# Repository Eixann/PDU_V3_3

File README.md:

**PDU_V3_3** is the power distribution board of the ORCA UGM underwater vehicle. It switches the 4S thruster battery
to 8 thruster ESCs through 8 Infineon PROFET+2 high-side switches (BTS70012-1ESP, one per thruster), measures the
current of every channel, and cuts all thrusters when the kill switch is pulled.

The PROFET channel and current-sense chain are copied from
[dingoPDM-Max](https://github.com/corygrant/dingoPDM-Max) (V1.2 schematic p.7-11).

- **Input:** QS8-S anti-spark connector (J1), soldered to a 5 mm copper VBAT busbar (BB1)
- **Outputs:** 4 right-angle XT60PW (J5-J8) + 2 stacked XT60 (J14, J15) for the upper board (V2_atas), 2 stacked XT60 GND (J12, J13)
- **Protection per channel:** short-circuit latch-off (~3 µs), over-temperature, BYG23M flyback, 10 nF output cap; SMCJ17A TVS on VBAT
- **Current sense:** IS → 1.2 kΩ → 3V3 zener clamp → LM324 follower → ADS7828 (12-bit, I2C 0x48) on J3
- **Kill:** XT30 (J2) switched battery → TSR 1-2450 → `KILL_EN` → IN/DEN of all 8 PROFETs

> [!WARNING]
> This board was designed by students for a research vehicle, not by a professional. Use it at your own risk; the
> designers are not responsible for damage or injury. The busbars (BB1, BB2, BB3) are **mandatory**: without them the
> copper reaches >100 °C at 14 A per thruster.

---

## Specifications

| Item | Value |
| --- | --- |
| Battery | 4S Li-ion/LiPo, 16.8 V max (PROFET V<sub>S(NOR)</sub> 6-18 V, abs. max 28 V) |
| Channels | 8 × BTS70012-1ESP, 1 thruster each |
| Design current | 14 A per thruster continuous (112 A total), simulated T<sub>j</sub> 58-61 °C with busbars |
| Board | 118.2 × 113.6 mm, 2 layers, 2 oz copper, 1.6 mm |
| Logic | +5 V (TSR 1-2450) → +3V3 (LD1117S33), always on |
| ADC | ADS7828 @ 0x48, internal reference on (PD1 = 1), I ≈ code / 58.3 A |
| Fault | latched fault reads ≥ 2000 codes (≈ 2950 typ.); reset = IN low ≥ 100 ms (pull the kill) |

---

## Channel Map

The OUT2/OUT3 connectors were swapped so every output lane stays on one copper layer. Firmware must use this table.

| Connector pin | Net / PROFET | ADS7828 channel |
| --- | --- | --- |
| J14.2 (stack) | OUT1 / U101 | CH7 |
| J5.2 | OUT2 / U201 | CH4 |
| J14.1 (stack) | OUT3 / U301 | CH5 |
| J6.2 | OUT4 / U401 | CH6 |
| J7.2 | OUT5 / U501 | CH1 |
| J8.2 | OUT6 / U601 | CH2 |
| J15.2 (stack) | OUT7 / U701 | CH0 |
| J15.1 (stack) | OUT8 / U801 | CH3 |

J3 (JST-XH 4p to the Jetson): pin 1 NC, pin 2 SDA, pin 3 SCL, pin 4 GND.

> [!IMPORTANT]
> The Jetson/Pixhawk run from a separate battery, but their ground is already joined to the thruster ground through
> the ESC PWM leads and J3. Bond the system ground to a BB2 GND bolt with one 18-20 AWG wire so this current does
> not flow in the thin signal wires, twist SDA/SCL and every PWM lead with its ground, and do not connect the ESC
> BEC (red) wires to the Pixhawk.

---

## Notes

- Open the project with **KiCad 9**. Saving it in KiCad 10 makes it unreadable for KiCad 9.
- The QS8-S footprint comes from a measured part; there is no official QS8-S drawing.
- Upper board: `V2_atas/` (PCB only, no schematic). It stacks on J14/J15 and carries 4 XT60PW outputs; its channel labels follow the OUT2/OUT3 swap in the Channel Map.
- Busbar cut drawing (BB1/BB2/BB3): `PDU_V3_3/PDU_V3_3_busbars.dxf`. Gerbers, BOM and pick-and-place are exported from KiCad.
- Bottom side:

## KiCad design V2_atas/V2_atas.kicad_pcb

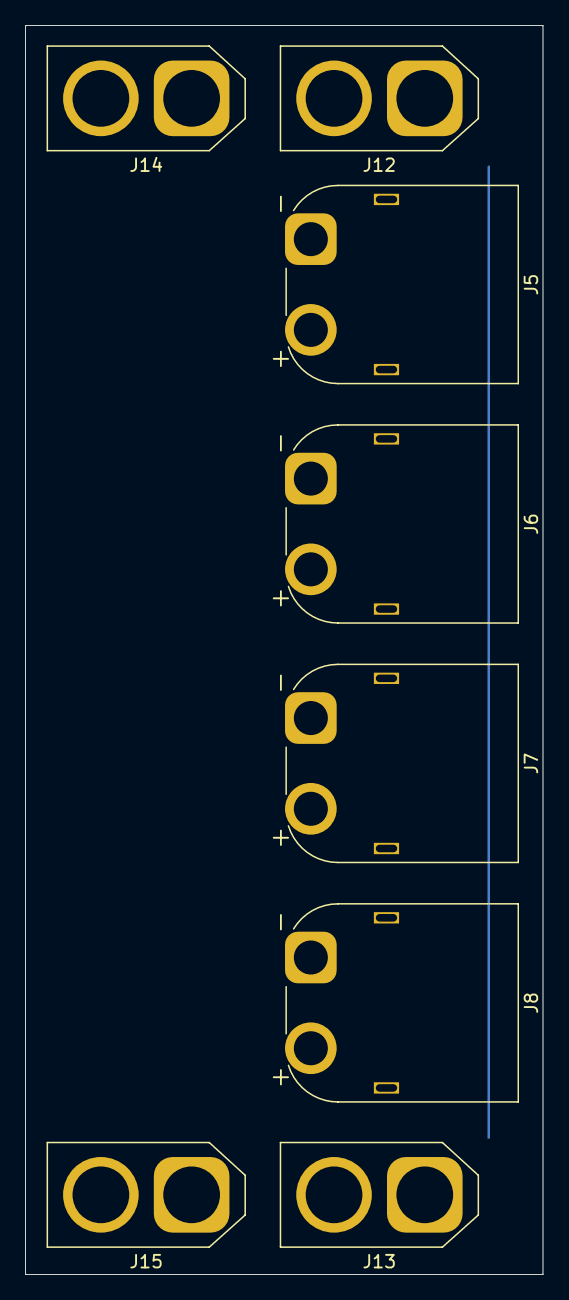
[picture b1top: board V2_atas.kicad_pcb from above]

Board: 2 copper layers, 41.1 x 99.1 mm, 8 parts (0 on the bottom side), 5 nets, no tracks yet.

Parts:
J5, J6, J7, J8: XT60-M; AMASS_XT60PW-M_1x02_P7.20mm_Horizontal
J12, J13, J14, J15: XT60-M; AMASS_XT60-M_1x02_P7.20mm_Vertical

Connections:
GND: J5.1 (NEG), J6.1 (NEG), J7.1 (NEG), J8.1 (NEG), J12.1 (NEG), J12.2 (POS), J13.1 (NEG), J13.2 (POS)
OUT1: J6.2 (POS), J14.2 (POS)
OUT3: J5.2 (POS), J14.1 (NEG)
OUT7: J7.2 (POS), J15.2 (POS)
OUT8: J8.2 (POS), J15.1 (NEG)

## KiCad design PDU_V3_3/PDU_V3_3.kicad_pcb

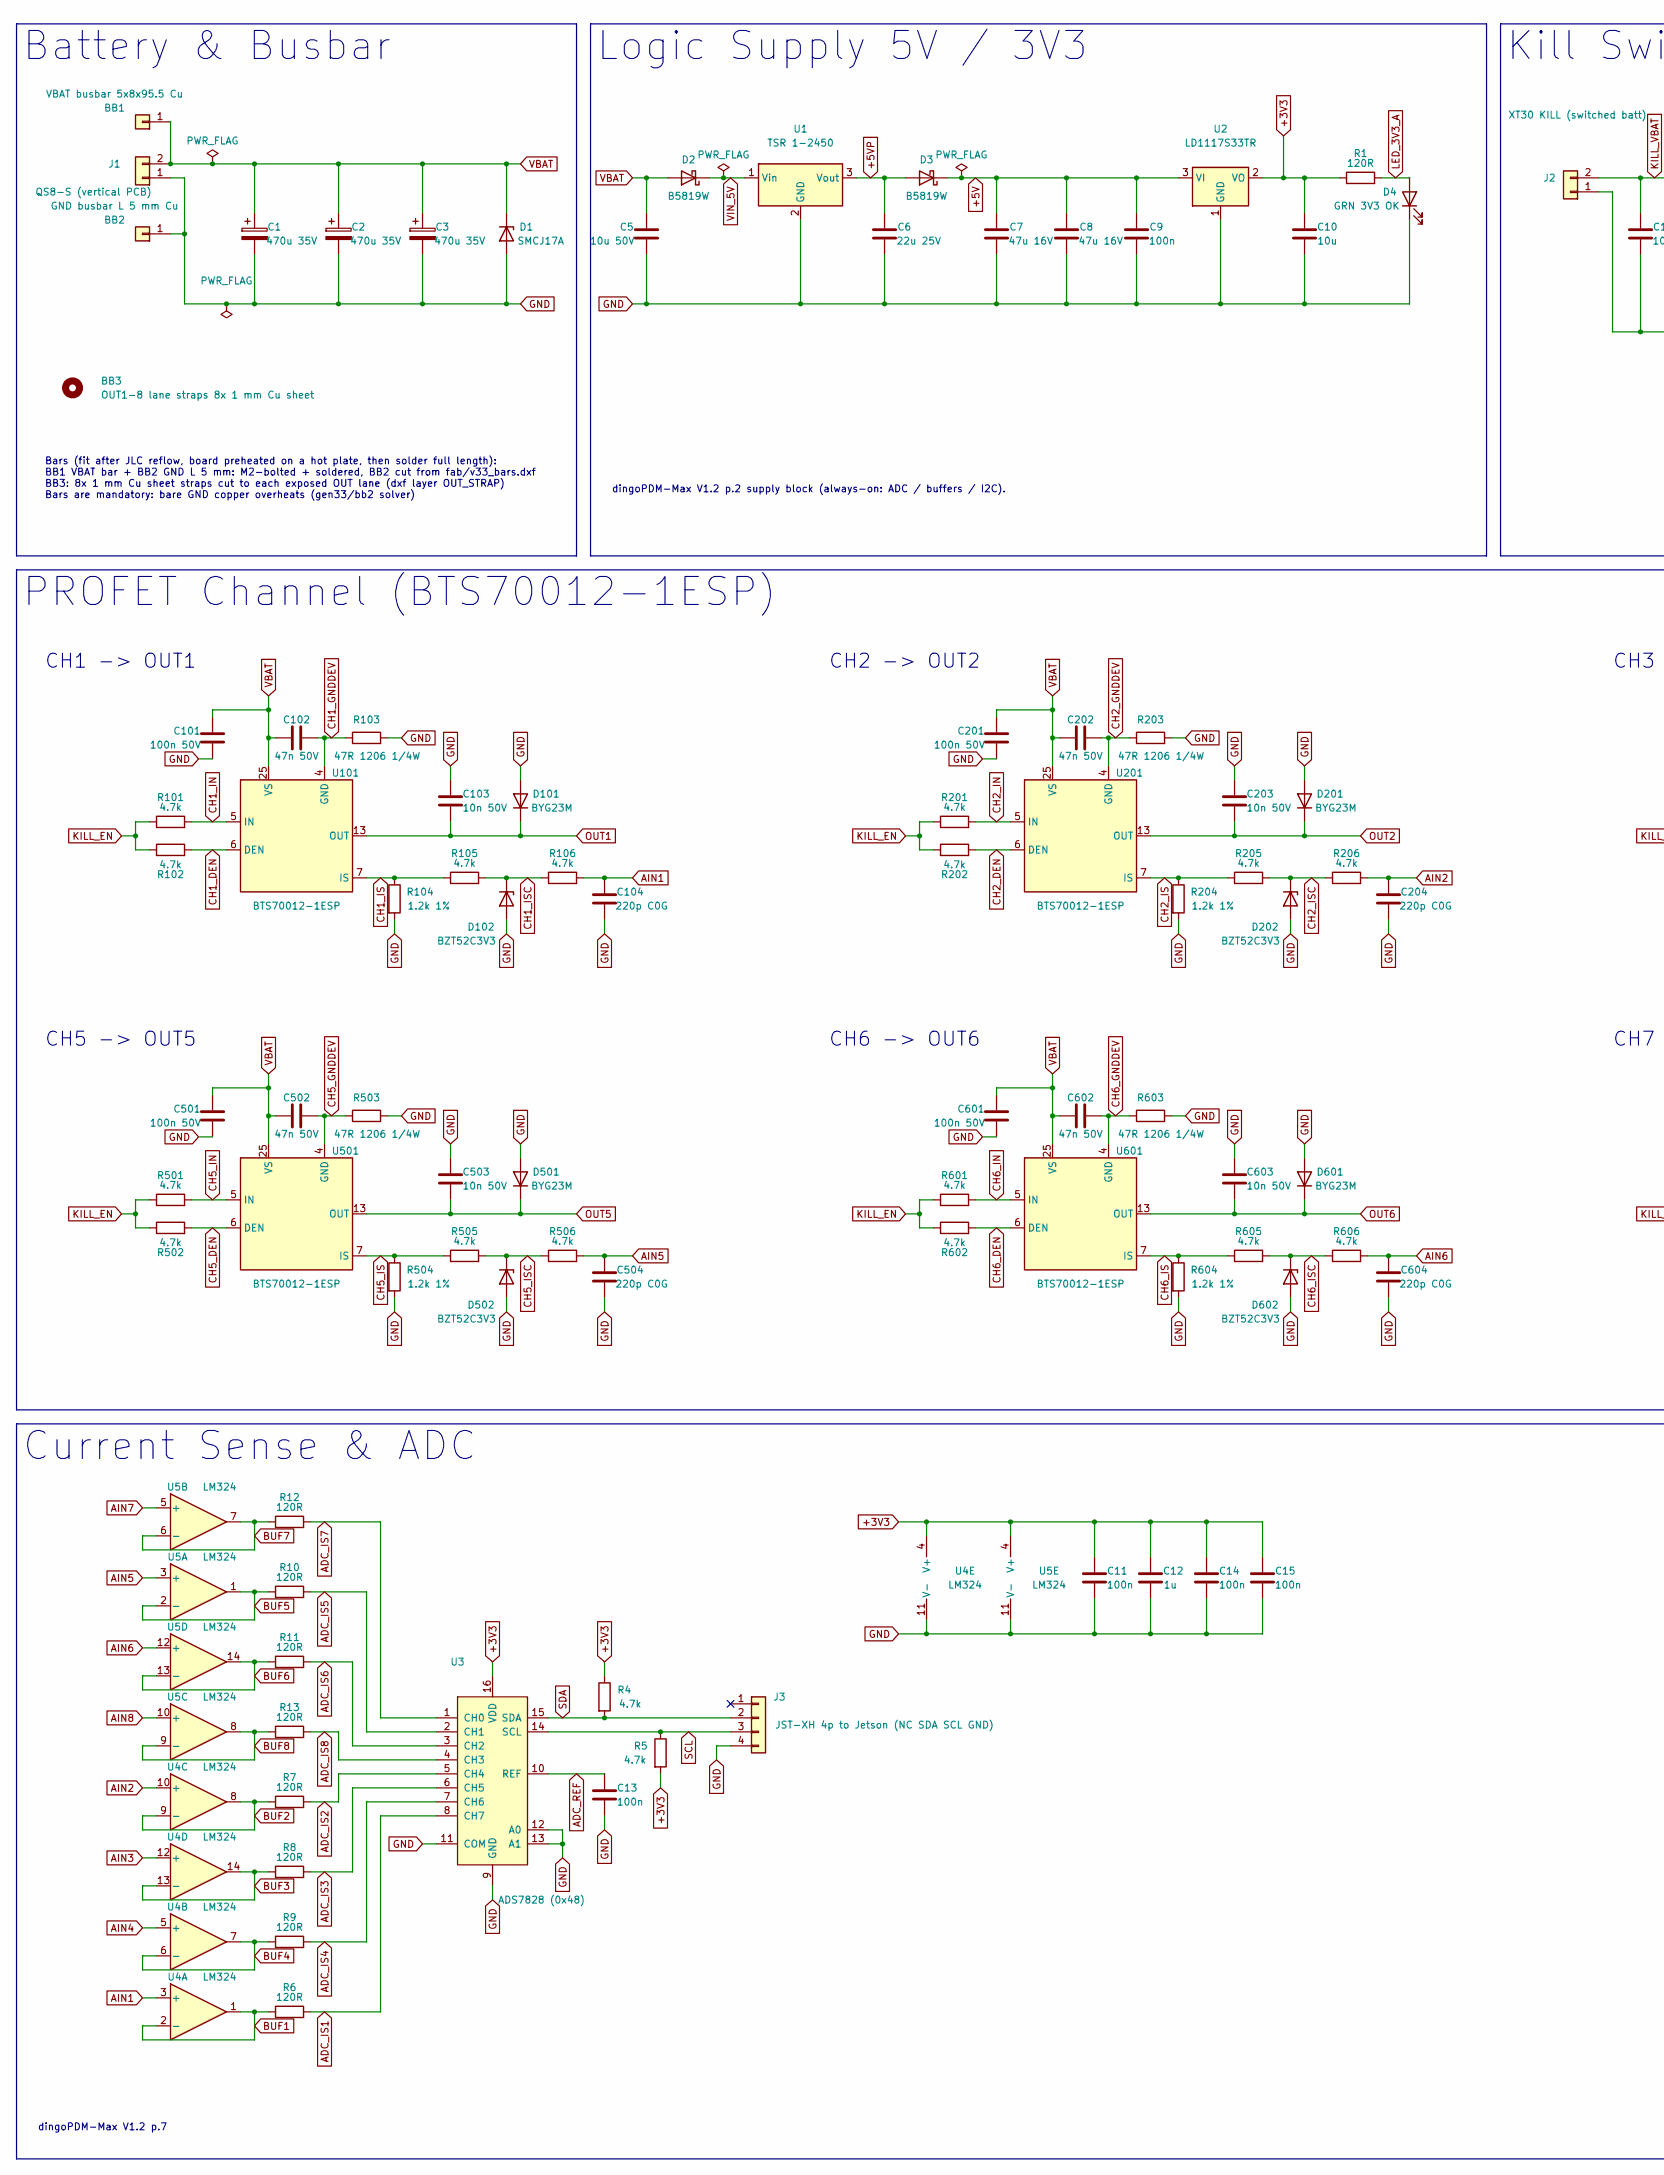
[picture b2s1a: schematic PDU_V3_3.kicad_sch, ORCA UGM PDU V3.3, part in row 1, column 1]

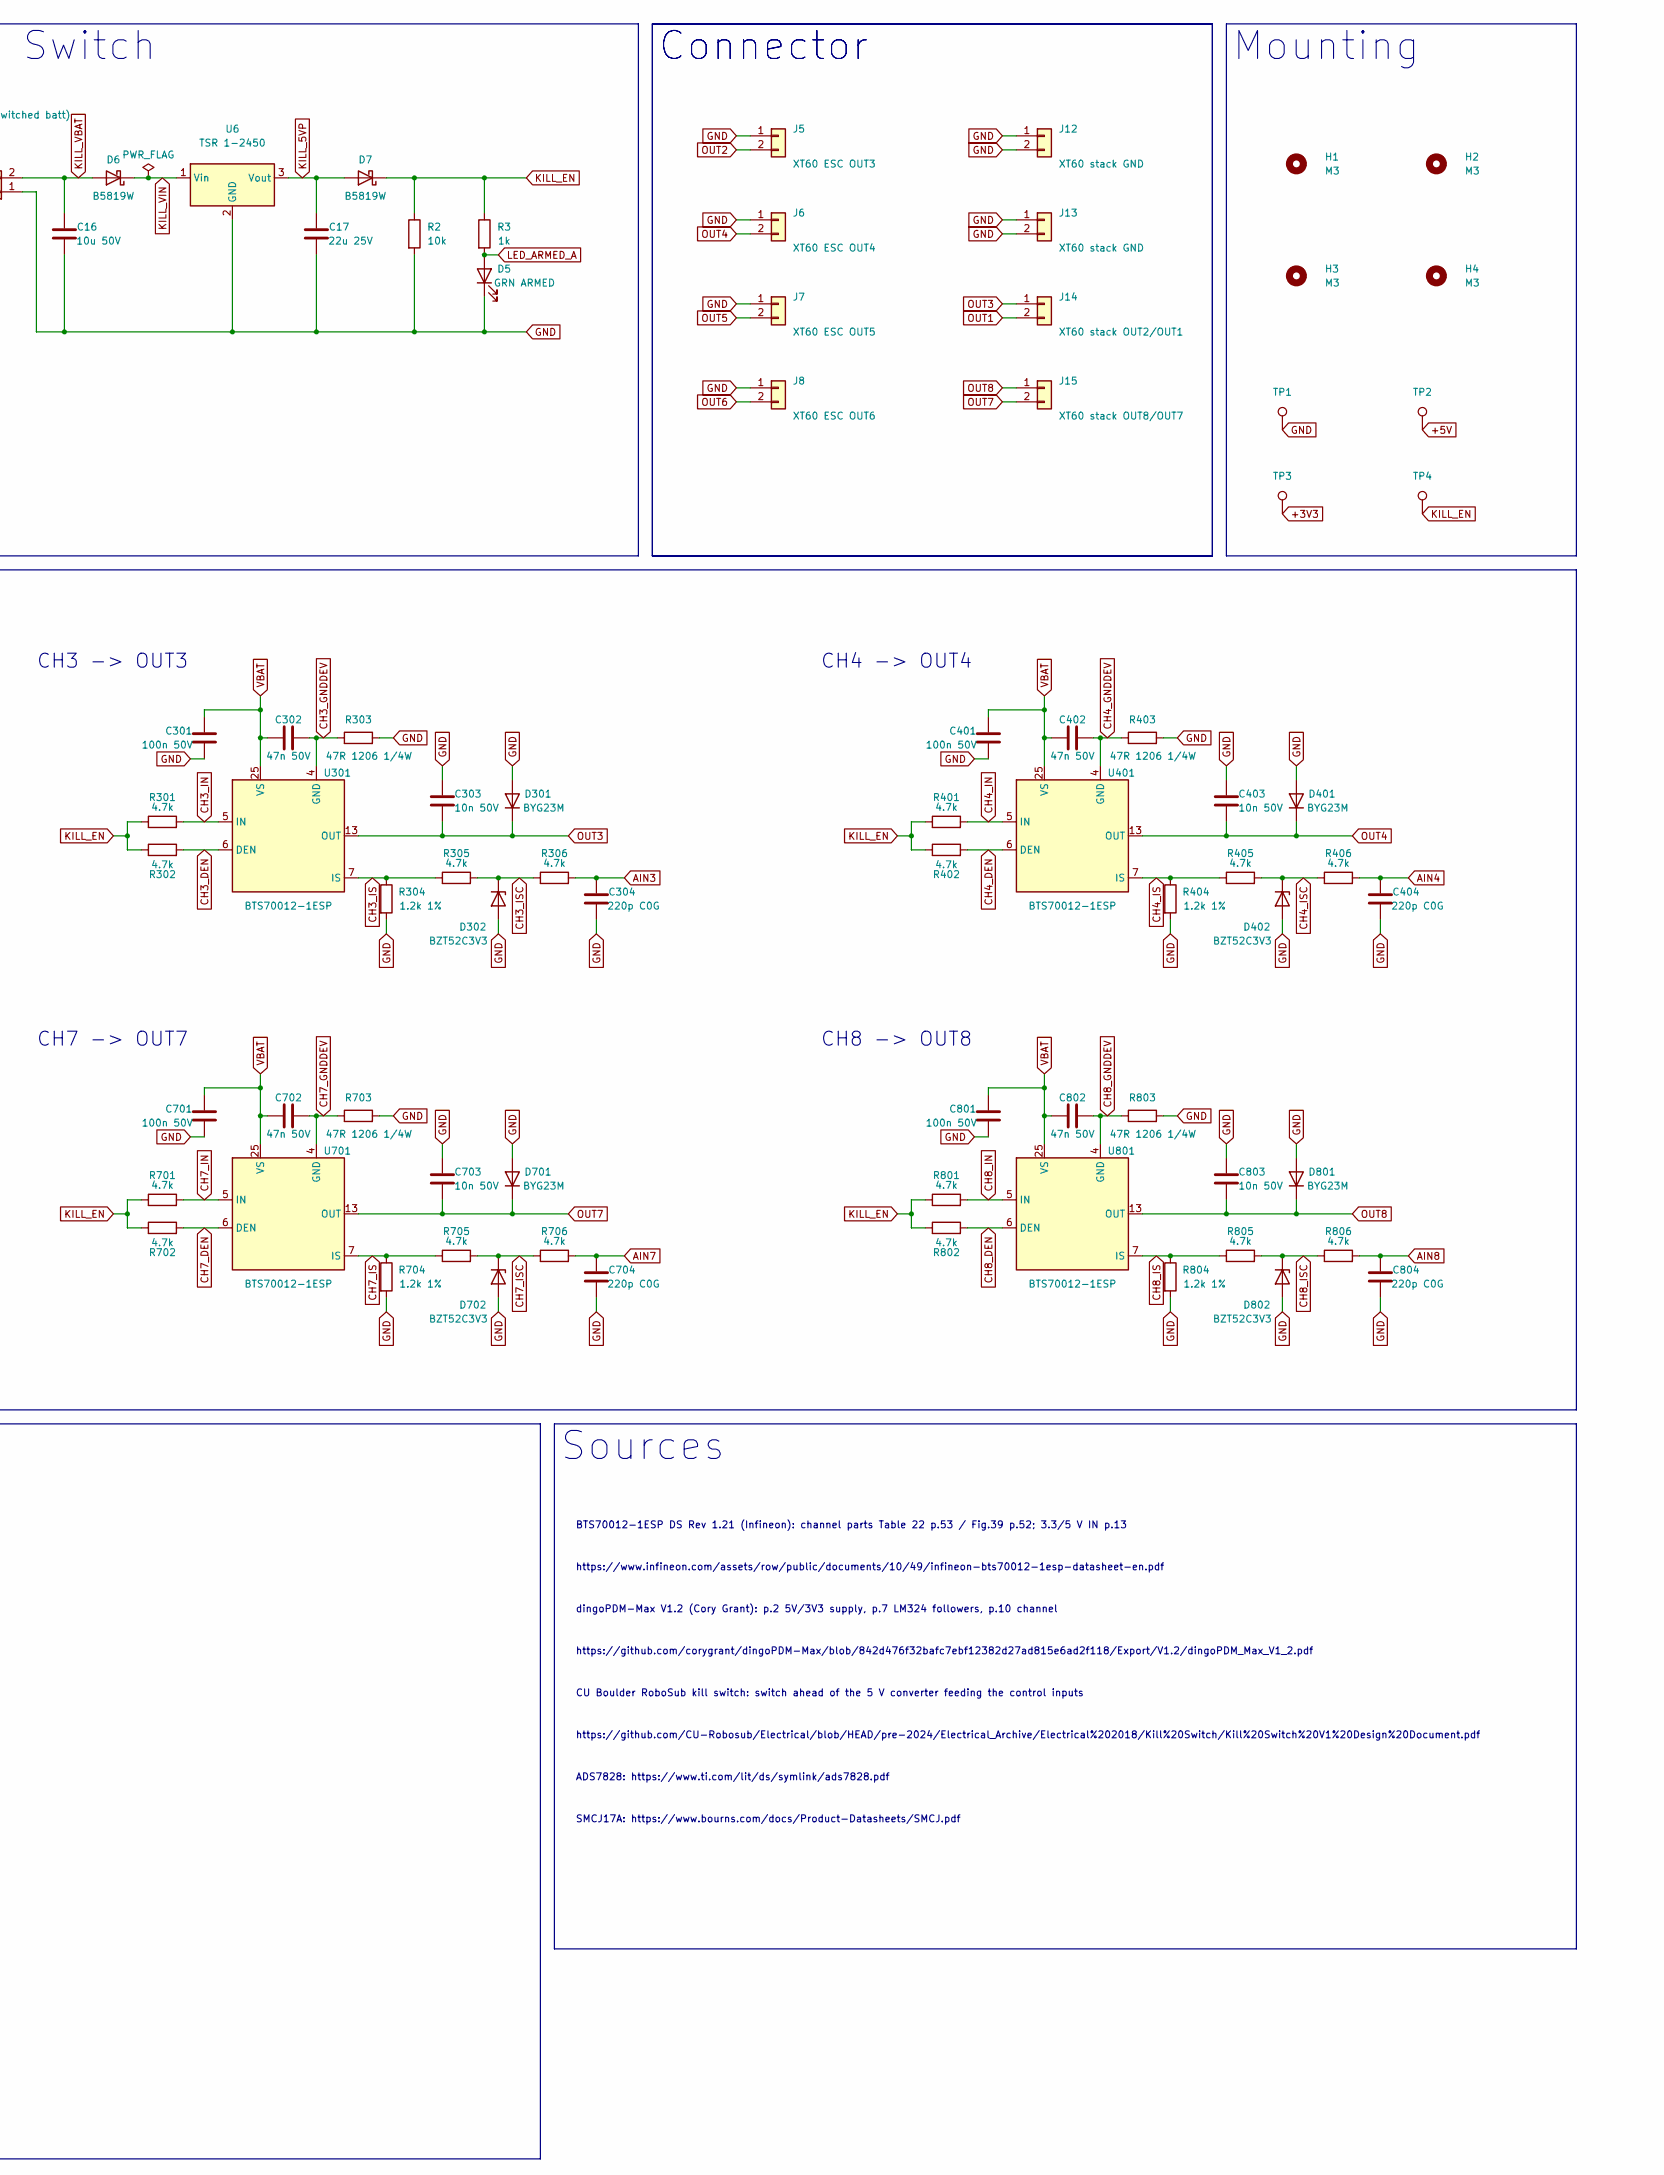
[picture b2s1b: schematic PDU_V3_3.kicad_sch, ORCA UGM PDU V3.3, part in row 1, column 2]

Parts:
BB1: VBAT busbar 5x8x95.5 Cu; Busbar_VBAT_5x8x92
BB2: GND busbar L 5 mm Cu; Busbar_GND_L_5x8
BB3: OUT1-8 lane straps 8x 1 mm Cu sheet
C1, C2, C3: 470u 35V; CP_Radial_D10.0mm_P5.00mm
C5, C16: 10u 50V; C_1206_3216Metric
C6, C17: 22u 25V; C_1206_3216Metric
C7, C8: 47u 16V; C_1206_3216Metric
C9, C11, C13, C14, C15: 100n; C_0603_1608Metric
C10: 10u; C_0805_2012Metric
C12: 1u; C_0603_1608Metric
C101, C201, C301, C401, C501, C601, C701, C801: 100n 50V; C_0603_1608Metric
C102, C202, C302, C402, C502, C602, C702, C802: 47n 50V; C_0603_1608Metric
C103, C203, C303, C403, C503, C603, C703, C803: 10n 50V; C_0603_1608Metric
C104, C204, C304, C404, C504, C604, C704, C804: 220p C0G; C_0603_1608Metric
D1: SMCJ17A; D_SMC
D2, D3, D6, D7: B5819W; D_SOD-123
D4: GRN 3V3 OK; LED_0603_1608Metric
D5: GRN ARMED; LED_0603_1608Metric
D101, D201, D301, D401, D501, D601, D701, D801: BYG23M; D_SMA
D102, D202, D302, D402, D502, D602, D702, D802: BZT52C3V3; D_SOD-123
H1, H2, H3, H4: M3; MountingHole_3.2mm_M3
J1: QS8-S (vertical PCB); AMASS_QS8S
J2: XT30 KILL (switched batt); AMASS_XT30PW-M_1x02_P2.50mm_Horizontal
J3: JST-XH 4p to Jetson (NC SDA SCL GND); JST_XH_B4B-XH-A_1x04_P2.50mm_Vertical
J5: XT60 ESC OUT3; AMASS_XT60PW-M_GNDpegs
J6: XT60 ESC OUT4; AMASS_XT60PW-M_GNDpegs
J7: XT60 ESC OUT5; AMASS_XT60PW-M_GNDpegs
J8: XT60 ESC OUT6; AMASS_XT60PW-M_GNDpegs
J12, J13: XT60 stack GND; AMASS_XT60-M_1x02_P7.20mm_Vertical
J14: XT60 stack OUT2/OUT1; AMASS_XT60-M_1x02_P7.20mm_Vertical
J15: XT60 stack OUT8/OUT7; AMASS_XT60-M_1x02_P7.20mm_Vertical
R1, R6, R7, R8, R9, R10, R11, R12, R13: 120R; R_0603_1608Metric
R2: 10k; R_0603_1608Metric
R3: 1k; R_0603_1608Metric
R4, R5, R101, R102, R105, R106, R201, R202, R205, R206, R301, R302, R305, R306, R401, R402, R405, R406, R501, R502, R505, R506, R601, R602, R605, R606, R701, R702, R705, R706, R801, R802, R805, R806: 4.7k; R_0603_1608Metric
R103, R203, R303, R403, R503, R603, R703, R803: 47R 1206 1/4W; R_1206_3216Metric
R104, R204, R304, R404, R504, R604, R704, R804: 1.2k 1%; R_0603_1608Metric
TP1: GND; TestPoint_Pad_D1.5mm
TP2: +5V; TestPoint_Pad_D1.5mm
TP3: +3V3; TestPoint_Pad_D1.5mm
TP4: KILL_EN; TestPoint_Pad_D1.5mm
U1, U6: TSR 1-2450; Converter_DCDC_TRACO_TSR-1_THT
U2: LD1117S33TR; SOT-223-3_TabPin2
U3: ADS7828 (0x48); TSSOP-16_4.4x5mm_P0.65mm
U4, U5: LM324; SOIC-14_3.9x8.7mm_P1.27mm
U101, U201, U301, U401, U501, U601, U701, U801: BTS70012-1ESP; Infineon_PG-TSDSO-24_ThermalVias

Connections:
+3V3: C10.1, C11.1, C12.1, C14.1, C15.1, R1.1, R4.1, R5.2, TP3.1, U2.2 (VO), U3.16 (VDD), U4.4 (V+), U5.4 (V+)
+5V: C7.1, C8.1, C9.1, D3.1 (K), TP2.1, U2.3 (VI)
+5VP: C6.1, D3.2 (A), U1.3 (Vout)
ADC_IS1: R6.2, U3.8 (CH7)
ADC_IS2: R7.2, U3.5 (CH4)
ADC_IS3: R8.2, U3.6 (CH5)
ADC_IS4: R9.2, U3.7 (CH6)
ADC_IS5: R10.2, U3.2 (CH1)
ADC_IS6: R11.2, U3.3 (CH2)
ADC_IS7: R12.2, U3.1 (CH0)
ADC_IS8: R13.2, U3.4 (CH3)
ADC_REF: C13.1, U3.10 (REF)
AIN1: C104.1, R106.2, U4.3 (+)
AIN2: C204.1, R206.2, U4.10 (+)
AIN3: C304.1, R306.2, U4.12 (+)
AIN4: C404.1, R406.2, U4.5 (+)
AIN5: C504.1, R506.2, U5.3 (+)
AIN6: C604.1, R606.2, U5.12 (+)
AIN7: C704.1, R706.2, U5.5 (+)
AIN8: C804.1, R806.2, U5.10 (+)
BUF1: R6.1, U4.1, U4.2 (-)
BUF2: R7.1, U4.8, U4.9 (-)
BUF3: R8.1, U4.13 (-), U4.14
BUF4: R9.1, U4.6 (-), U4.7
BUF5: R10.1, U5.1, U5.2 (-)
BUF6: R11.1, U5.13 (-), U5.14
BUF7: R12.1, U5.6 (-), U5.7
BUF8: R13.1, U5.8, U5.9 (-)
CH1_DEN: R102.2, U101.6 (DEN)
CH1_GNDDEV: C102.2, R103.1, U101.4 (GND)
CH1_IN: R101.2, U101.5 (IN)
CH1_IS: R104.1, R105.1, U101.7 (IS)
CH1_ISC: D102.1 (K), R105.2, R106.1
CH2_DEN: R202.2, U201.6 (DEN)
CH2_GNDDEV: C202.2, R203.1, U201.4 (GND)
CH2_IN: R201.2, U201.5 (IN)
CH2_IS: R204.1, R205.1, U201.7 (IS)
CH2_ISC: D202.1 (K), R205.2, R206.1
CH3_DEN: R302.2, U301.6 (DEN)
CH3_GNDDEV: C302.2, R303.1, U301.4 (GND)
CH3_IN: R301.2, U301.5 (IN)
CH3_IS: R304.1, R305.1, U301.7 (IS)
CH3_ISC: D302.1 (K), R305.2, R306.1
CH4_DEN: R402.2, U401.6 (DEN)
CH4_GNDDEV: C402.2, R403.1, U401.4 (GND)
CH4_IN: R401.2, U401.5 (IN)
CH4_IS: R404.1, R405.1, U401.7 (IS)
CH4_ISC: D402.1 (K), R405.2, R406.1
CH5_DEN: R502.2, U501.6 (DEN)
CH5_GNDDEV: C502.2, R503.1, U501.4 (GND)
CH5_IN: R501.2, U501.5 (IN)
CH5_IS: R504.1, R505.1, U501.7 (IS)
CH5_ISC: D502.1 (K), R505.2, R506.1
CH6_DEN: R602.2, U601.6 (DEN)
CH6_GNDDEV: C602.2, R603.1, U601.4 (GND)
CH6_IN: R601.2, U601.5 (IN)
CH6_IS: R604.1, R605.1, U601.7 (IS)
CH6_ISC: D602.1 (K), R605.2, R606.1
CH7_DEN: R702.2, U701.6 (DEN)
CH7_GNDDEV: C702.2, R703.1, U701.4 (GND)
CH7_IN: R701.2, U701.5 (IN)
CH7_IS: R704.1, R705.1, U701.7 (IS)
CH7_ISC: D702.1 (K), R705.2, R706.1
CH8_DEN: R802.2, U801.6 (DEN)
CH8_GNDDEV: C802.2, R803.1, U801.4 (GND)
CH8_IN: R801.2, U801.5 (IN)
CH8_IS: R804.1, R805.1, U801.7 (IS)
CH8_ISC: D802.1 (K), R805.2, R806.1
GND: BB2.1, C1.2, C2.2, C3.2, C5.2, C6.2, C7.2, C8.2, C9.2, C10.2, C11.2, C12.2, C13.2, C14.2, C15.2, C16.2, C17.2, C101.2, C103.2, C104.2, C201.2, C203.2, C204.2, C301.2, C303.2, C304.2, C401.2, C403.2, C404.2, C501.2, C503.2, C504.2, C601.2, C603.2, C604.2, C701.2, C703.2, C704.2, C801.2, C803.2, C804.2, D1.2 (A), D4.1 (K), D5.1 (K), D101.2 (A), D102.2 (A), D201.2 (A), D202.2 (A), D301.2 (A), D302.2 (A), D401.2 (A), D402.2 (A), D501.2 (A), D502.2 (A), D601.2 (A), D602.2 (A), D701.2 (A), D702.2 (A), D801.2 (A), D802.2 (A), J1.1, J2.1, J3.4, J5.1, J6.1, J7.1, J8.1, J12.1, J12.2, J13.1, J13.2, R2.2, R103.2, R104.2, R203.2, R204.2, R303.2, R304.2, R403.2, R404.2, R503.2, R504.2, R603.2, R604.2, R703.2, R704.2, R803.2, R804.2, TP1.1, U1.2 (GND), U2.1 (GND), U3.9 (GND), U3.11 (COM), U3.12 (A0), U3.13 (A1), U4.11 (V-), U5.11 (V-), U6.2 (GND)
KILL_5VP: C17.1, D7.2 (A), U6.3 (Vout)
KILL_EN: D7.1 (K), R2.1, R3.1, R101.1, R102.1, R201.1, R202.1, R301.1, R302.1, R401.1, R402.1, R501.1, R502.1, R601.1, R602.1, R701.1, R702.1, R801.1, R802.1, TP4.1
KILL_VBAT: C16.1, D6.2 (A), J2.2
KILL_VIN: D6.1 (K), U6.1 (Vin)
LED_3V3_A: D4.2 (A), R1.2
LED_ARMED_A: D5.2 (A), R3.2
OUT1: C103.1, D101.1 (K), J14.2, U101.13 (OUT), U101.14 (OUT), U101.15 (OUT), U101.16 (OUT), U101.17 (OUT), U101.18 (OUT), U101.19 (OUT), U101.20 (OUT), U101.21 (OUT), U101.22 (OUT), U101.23 (OUT), U101.24 (OUT)
OUT2: C203.1, D201.1 (K), J5.2, U201.13 (OUT), U201.14 (OUT), U201.15 (OUT), U201.16 (OUT), U201.17 (OUT), U201.18 (OUT), U201.19 (OUT), U201.20 (OUT), U201.21 (OUT), U201.22 (OUT), U201.23 (OUT), U201.24 (OUT)
OUT3: C303.1, D301.1 (K), J14.1, U301.13 (OUT), U301.14 (OUT), U301.15 (OUT), U301.16 (OUT), U301.17 (OUT), U301.18 (OUT), U301.19 (OUT), U301.20 (OUT), U301.21 (OUT), U301.22 (OUT), U301.23 (OUT), U301.24 (OUT)
OUT4: C403.1, D401.1 (K), J6.2, U401.13 (OUT), U401.14 (OUT), U401.15 (OUT), U401.16 (OUT), U401.17 (OUT), U401.18 (OUT), U401.19 (OUT), U401.20 (OUT), U401.21 (OUT), U401.22 (OUT), U401.23 (OUT), U401.24 (OUT)
OUT5: C503.1, D501.1 (K), J7.2, U501.13 (OUT), U501.14 (OUT), U501.15 (OUT), U501.16 (OUT), U501.17 (OUT), U501.18 (OUT), U501.19 (OUT), U501.20 (OUT), U501.21 (OUT), U501.22 (OUT), U501.23 (OUT), U501.24 (OUT)
OUT6: C603.1, D601.1 (K), J8.2, U601.13 (OUT), U601.14 (OUT), U601.15 (OUT), U601.16 (OUT), U601.17 (OUT), U601.18 (OUT), U601.19 (OUT), U601.20 (OUT), U601.21 (OUT), U601.22 (OUT), U601.23 (OUT), U601.24 (OUT)
OUT7: C703.1, D701.1 (K), J15.2, U701.13 (OUT), U701.14 (OUT), U701.15 (OUT), U701.16 (OUT), U701.17 (OUT), U701.18 (OUT), U701.19 (OUT), U701.20 (OUT), U701.21 (OUT), U701.22 (OUT), U701.23 (OUT), U701.24 (OUT)
OUT8: C803.1, D801.1 (K), J15.1, U801.13 (OUT), U801.14 (OUT), U801.15 (OUT), U801.16 (OUT), U801.17 (OUT), U801.18 (OUT), U801.19 (OUT), U801.20 (OUT), U801.21 (OUT), U801.22 (OUT), U801.23 (OUT), U801.24 (OUT)
SCL: J3.3, R5.1, U3.14 (SCL)
SDA: J3.2, R4.2, U3.15 (SDA)
VBAT: BB1.1, C1.1, C2.1, C3.1, C5.1, C101.1, C102.1, C201.1, C202.1, C301.1, C302.1, C401.1, C402.1, C501.1, C502.1, C601.1, C602.1, C701.1, C702.1, C801.1, C802.1, D1.1 (K), D2.2 (A), J1.2, U101.25 (VS), U201.25 (VS), U301.25 (VS), U401.25 (VS), U501.25 (VS), U601.25 (VS), U701.25 (VS), U801.25 (VS)
VIN_5V: D2.1 (K), U1.1 (Vin)

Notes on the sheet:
CH5 -> OUT5
dingoPDM-Max V1.2 p.2 supply block (always-on: ADC / buffers / I2C).
CH2 -> OUT2
SMCJ17A: https://www.bourns.com/docs/Product-Datasheets/SMCJ.pdf
CH7 -> OUT7
https://github.com/corygrant/dingoPDM-Max/blob/842d476f32bafc7ebf12382d27ad815e6ad2f118/Export/V1.2/dingoPDM_Max_V1_2.pdf
https://github.com/CU-Robosub/Electrical/blob/HEAD/pre-2024/Electrical_Archive/Electrical%202018/Kill%20Switch/Kill%20Switch%20V1%20Design%20Document.pdf
ADS7828: https://www.ti.com/lit/ds/symlink/ads7828.pdf
dingoPDM-Max V1.2 p.7
CU Boulder RoboSub kill switch: switch ahead of the 5 V converter feeding the control inputs
CH8 -> OUT8
BTS70012-1ESP DS Rev 1.21 (Infineon): channel parts Table 22 p.53 / Fig.39 p.52; 3.3/5 V IN p.13
https://www.infineon.com/assets/row/public/documents/10/49/infineon-bts70012-1esp-datasheet-en.pdf
CH6 -> OUT6
dingoPDM-Max V1.2 (Cory Grant): p.2 5V/3V3 supply, p.7 LM324 followers, p.10 channel
CH1 -> OUT1
CH3 -> OUT3
CH4 -> OUT4
Bars (fit after JLC reflow, board preheated on a hot plate, then solder full length): BB1 VBAT bar + BB2 GND L 5 mm: M2-bolted + soldered, BB2 cut from fab/v33_bars.dxf BB3: 8x 1 mm Cu sheet straps cut to each exposed OUT lane (dxf layer OUT_STRAP) Bars are mandatory: bare GND copper overheats (gen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
Battery & Busbar
Logic Supply 5V / 3V3
Current Sense & ADC
PROFET Channel (BTS70012-1ESP)
Connector
Mounting
Kill Switch
Sources

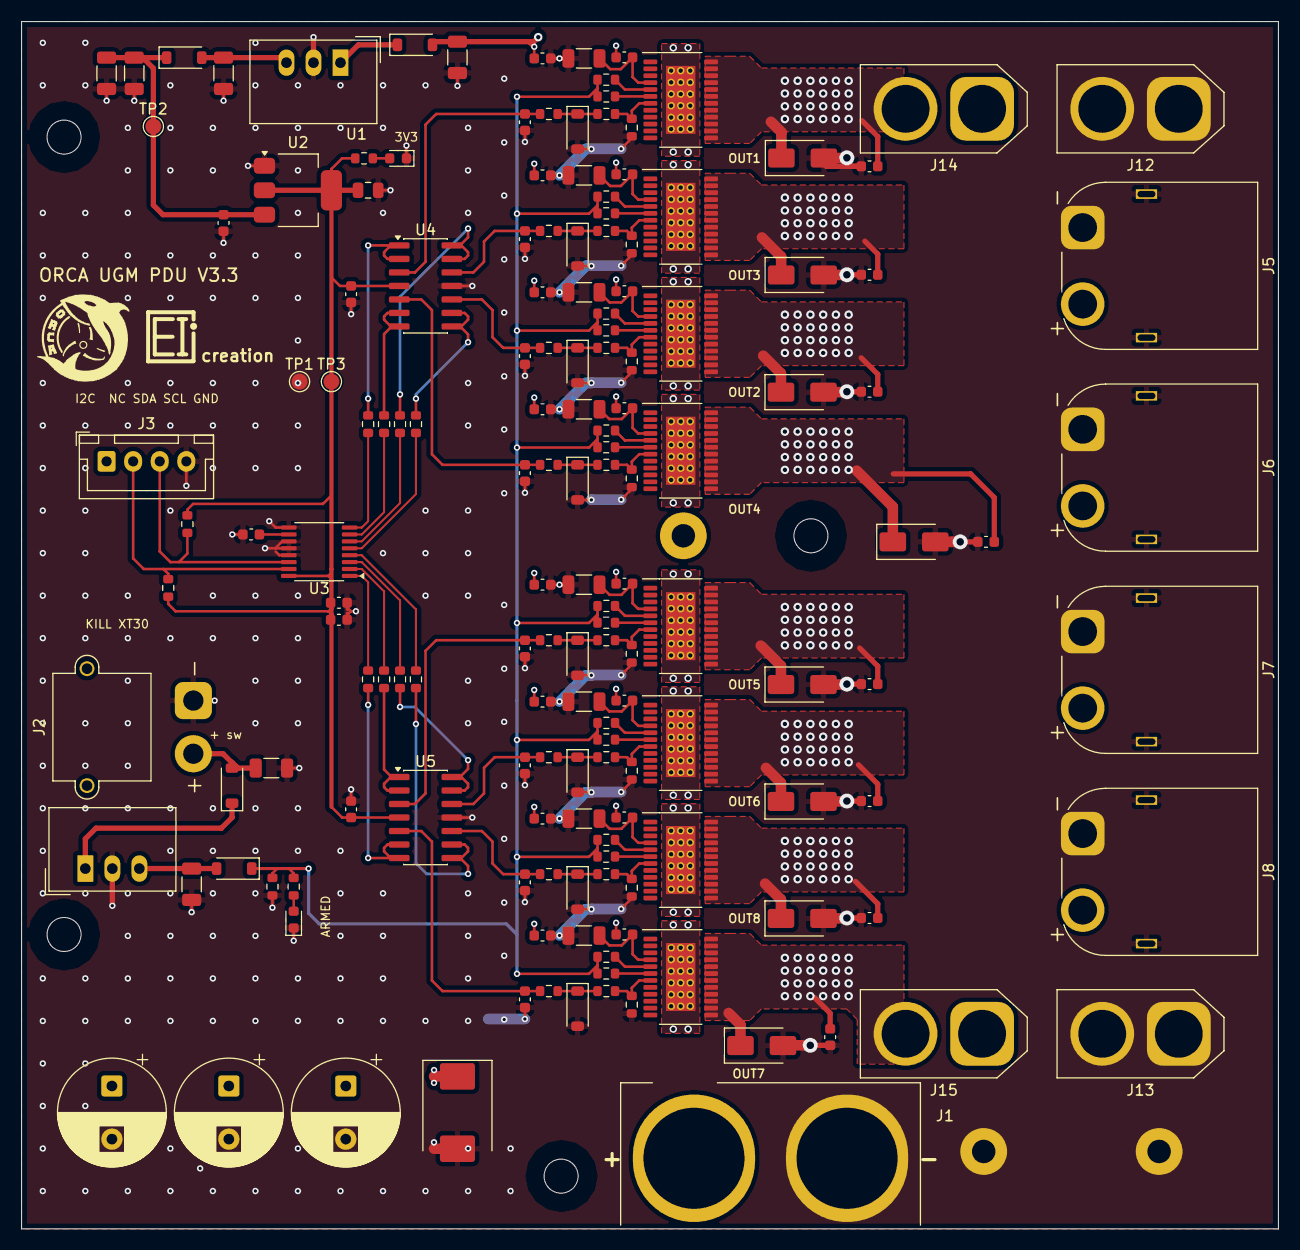
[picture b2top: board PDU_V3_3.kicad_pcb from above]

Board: 2 copper layers, 118.2 x 113.6 mm, 169 parts (1 on the bottom side), 87 nets.

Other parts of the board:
LOGO1: ORCA_logo; LOGO_ORCA
LOGO2: Ei_logo; LOGO_Ei

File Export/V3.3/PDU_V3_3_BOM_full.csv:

"Reference","Value","Footprint","QUANTITY","LCSC","MPN","Manufacturer","DNP"
"BB1","VBAT busbar 5x8x95.5 Cu","V3_3:Busbar_VBAT_5x8x92","1","","","",""
"BB2","GND busbar L 5 mm Cu","V3_3:Busbar_GND_L_5x8","1","","","",""
"BB3","OUT1-8 lane straps 8x 1 mm Cu sheet","","1","","","",""
"C1-C3","470u 35V","Capacitor_THT:CP_Radial_D10.0mm_P5.00mm","3","","","",""
"C5,C16","10u 50V","Capacitor_SMD:C_1206_3216Metric","2","","","",""
"C6,C17","22u 25V","Capacitor_SMD:C_1206_3216Metric","2","","","",""
"C7,C8","47u 16V","Capacitor_SMD:C_1206_3216Metric","2","","","",""
"C9,C11,C13-C15","100n","Capacitor_SMD:C_0603_1608Metric","5","","","",""
"C10","10u","Capacitor_SMD:C_0805_2012Metric","1","","","",""
"C12","1u","Capacitor_SMD:C_0603_1608Metric","1","","","",""
"C101,C201,C301,C401,C501,C601,C701,C801","100n 50V","Capacitor_SMD:C_0603_1608Metric","8","","","",""
"C102,C202,C302,C402,C502,C602,C702,C802","47n 50V","Capacitor_SMD:C_0603_1608Metric","8","","","",""
"C103,C203,C303,C403,C503,C603,C703,C803","10n 50V","Capacitor_SMD:C_0603_1608Metric","8","","","",""
"C104,C204,C304,C404,C504,C604,C704,C804","220p C0G","Capacitor_SMD:C_0603_1608Metric","8","","","",""
"D1","SMCJ17A","Diode_SMD:D_SMC","1","","","",""
"D2,D3,D6,D7","B5819W","Diode_SMD:D_SOD-123","4","","","",""
"D4","GRN 3V3 OK","LED_SMD:LED_0603_1608Metric","1","","","",""
"D5","GRN ARMED","LED_SMD:LED_0603_1608Metric","1","","","",""
"D101,D201,D301,D401,D501,D601,D701,D801","BYG23M","Diode_SMD:D_SMA","8","","","",""
"D102,D202,D302,D402,D502,D602,D702,D802","BZT52C3V3","Diode_SMD:D_SOD-123","8","","","",""
"J1","QS8-S (vertical PCB)","V3_3:AMASS_QS8S","1","","","",""
"J2","XT30 KILL (switched batt)","Connector_AMASS:AMASS_XT30PW-M_1x02_P2.50mm_Horizontal","1","","","",""
"J3","JST-XH 4p to Jetson (NC SDA SCL GND)","Connector_JST:JST_XH_B4B-XH-A_1x04_P2.50mm_Vertical","1","","","",""
"J5","XT60 ESC OUT3","V3_3:AMASS_XT60PW-M_GNDpegs","1","","","",""
"J6","XT60 ESC OUT4","V3_3:AMASS_XT60PW-M_GNDpegs","1","","","",""
"J7","XT60 ESC OUT5","V3_3:AMASS_XT60PW-M_GNDpegs","1","","","",""
"J8","XT60 ESC OUT6","V3_3:AMASS_XT60PW-M_GNDpegs","1","","","",""
"J12,J13","XT60 stack GND","Connector_AMASS:AMASS_XT60-M_1x02_P7.20mm_Vertical","2","","","",""
"J14","XT60 stack OUT2/OUT1","Connector_AMASS:AMASS_XT60-M_1x02_P7.20mm_Vertical","1","","","",""
"J15","XT60 stack OUT8/OUT7","Connector_AMASS:AMASS_XT60-M_1x02_P7.20mm_Vertical","1","","","",""
"R1,R6-R13","120R","Resistor_SMD:R_0603_1608Metric","9","","","",""
"R2","10k","Resistor_SMD:R_0603_1608Metric","1","","","",""
"R3","1k","Resistor_SMD:R_0603_1608Metric","1","","","",""
"R4,R5,R101,R102,R105,R106,R201,R202,R205,R206,R301,R302,R305,R306,R401,R402,R405,R406,R501,R502,R505,R506,R601,R602,R605,R606,R701,R702,R705,R706,R801,R802,R805,R806","4.7k","Resistor_SMD:R_0603_1608Metric","34","","","",""
"R103,R203,R303,R403,R503,R603,R703,R803","47R 1206 1/4W","Resistor_SMD:R_1206_3216Metric","8","","","",""
"R104,R204,R304,R404,R504,R604,R704,R804","1.2k 1%","Resistor_SMD:R_0603_1608Metric","8","","","",""
"U1,U6","TSR 1-2450","Converter_DCDC:Converter_DCDC_TRACO_TSR-1_THT","2","","","",""
"U2","LD1117S33TR","Package_TO_SOT_SMD:SOT-223-3_TabPin2","1","","","",""
"U3","ADS7828 (0x48)","Package_SO:TSSOP-16_4.4x5mm_P0.65mm","1","","","",""
"U4,U5","LM324","Package_SO:SOIC-14_3.9x8.7mm_P1.27mm","2","","","",""
"U101,U201,U301,U401,U501,U601,U701,U801","BTS70012-1ESP","V3_3:Infineon_PG-TSDSO-24_ThermalVias","8","","","",""
